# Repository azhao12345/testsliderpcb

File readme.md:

moved to [gitlab](https://gitlab.com/azhao12345/testsliderpcb)

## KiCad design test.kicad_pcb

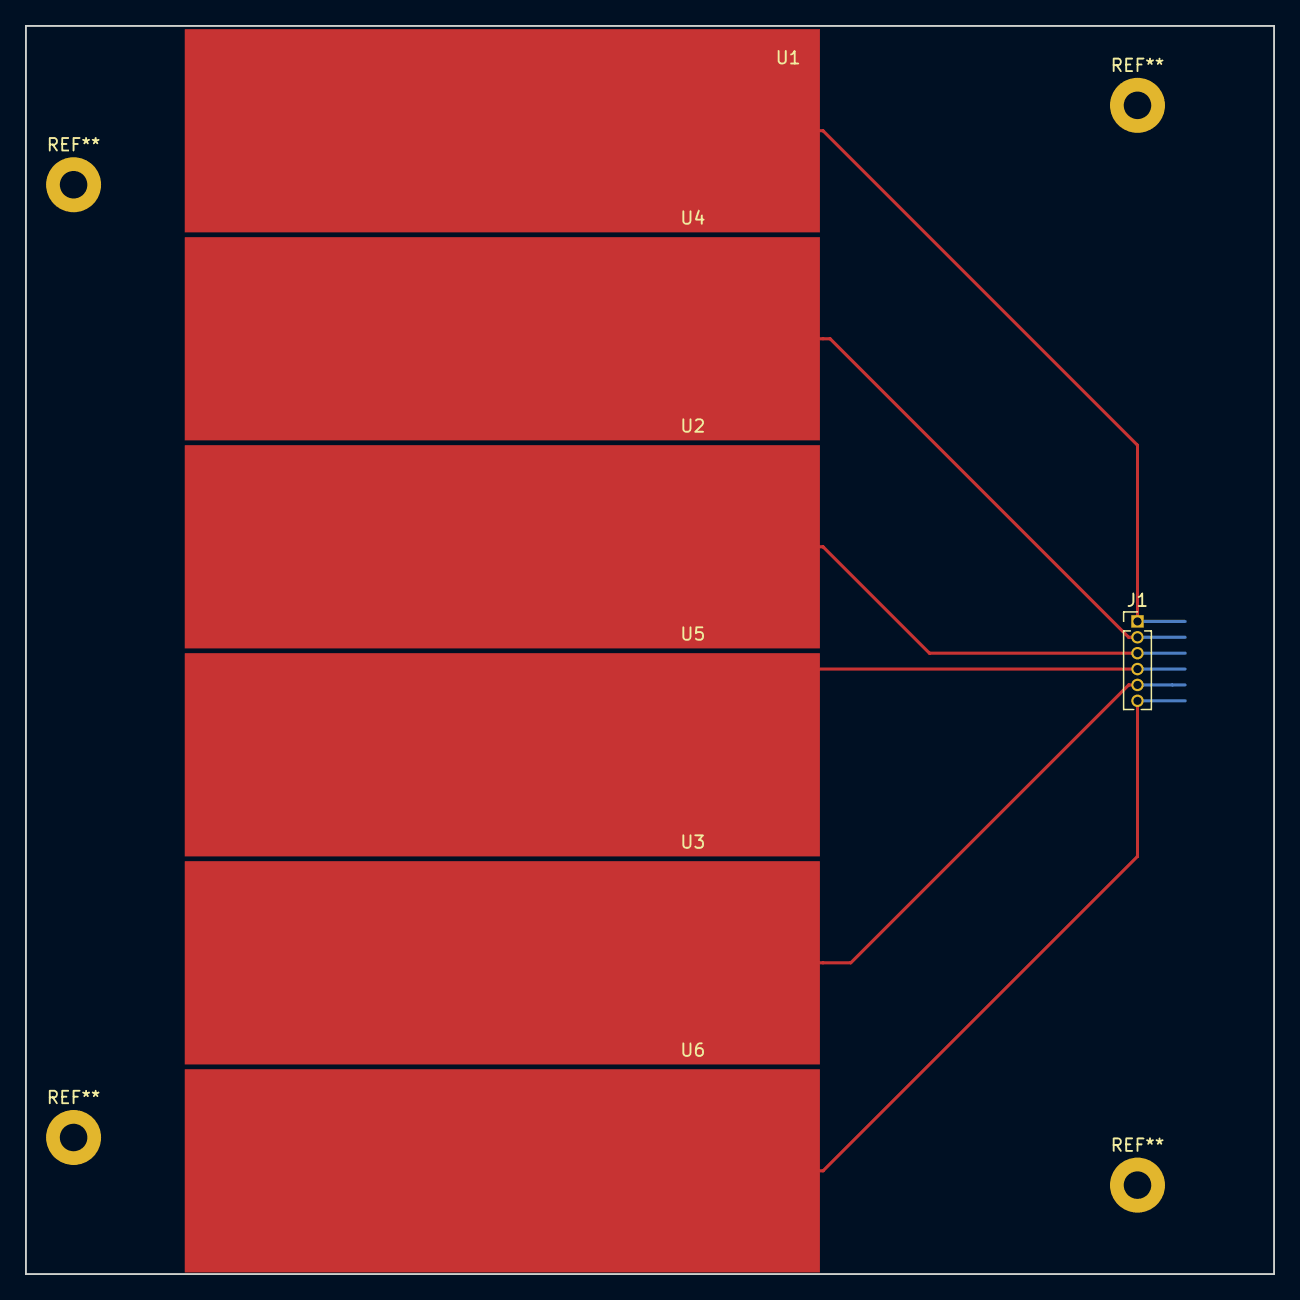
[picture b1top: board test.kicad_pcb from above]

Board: 2 copper layers, 99.8 x 99.8 mm, 8 parts (1 on the bottom side), 6 nets.

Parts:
J1: Conn_01x06_Male; PinHeader_1x06_P1.27mm_Vertical
J2: Conn_01x06_Male; testtt
U1, U2, U3, U4, U5, U6: testsensorg; sensorg

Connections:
unnamed: J1.1, J2.1, U1.1
unnamed: J1.2, J2.2, U4.1
unnamed: J1.3, J2.3, U2.1
unnamed: J1.4, J2.4, U5.1
unnamed: J1.5, J2.5, U3.1
unnamed: J1.6, J2.6, U6.1

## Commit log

2019-01-14 initial
2020-01-11 move
